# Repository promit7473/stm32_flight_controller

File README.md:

# STM32 Autonomous Quadcopter Flight Controller

A bare-metal flight controller for a quadcopter, running a **250 Hz** control
loop on an STM32F103C8T6 (Cortex-M3, 72 MHz, no FPU). It fuses a gyroscope,
accelerometer, magnetometer, barometer and GPS into an attitude and position
estimate, and closes six control loops around it: three rate loops, an
attitude cascade, altitude hold, and GPS position hold.

No flight stack, no RTOS, no libraries beyond `Wire` and `EEPROM`. Every
transform, filter and controller here is written out explicitly, which is why
this document can state exactly what the aircraft computes on each of its
250 loops per second.

Built in 2023, then flown, re-tuned and upgraded repeatedly across my
undergraduate years. The airframe, wiring and gains in this repository are the
state it reached after those iterations, not a first attempt.

<p align="center">
  <em>Take-off under its own control.
  Full 18 s flight: <a href="media/test_flight_540p.mp4">test_flight_540p.mp4</a></em>
</p>

<p align="center">
  <em>Hand-soldered on perfboard: STM32 board, MPU-6050, MS5611, HMC5883L,
  GPS and the 433 MHz telemetry radio, wired to four ESCs.</em>
</p>

---

## Hardware

### Module-carrier PCB — Rev A prototype

The new carrier is a **90 × 70 mm, two-layer PCB** for the Blue Pill and
plug-in IMU, compass and barometer modules, with connectors for GPS, telemetry,
a PPM-sum receiver and four ESCs. It is intended for an F450-style build;
the 80 × 60 mm mounting pattern requires a verified adapter or standoffs,
not an assumed direct fit to the frame.

These are **CAD previews, not photographs of built hardware**. The Blue Pill
uses a detailed community model; the three sensor modules are illustrative
approximations. The historical flight photos above show the earlier perfboard
controller, not validation of this new PCB.

- [KiCad project, PCB and assembly notes](hardware/stm32_f450_carrier_rev_a/README.md)
- [Gerbers and drill files](hardware/stm32_f450_carrier_rev_a/fabrication/)
  · [downloadable fabrication ZIP](hardware/stm32_f450_carrier_rev_a/stm32_f450_carrier_rev_a_gerbers.zip)
- [BOM](hardware/stm32_f450_carrier_rev_a/BOM.csv)
  · [connector pin map](hardware/stm32_f450_carrier_rev_a/pinmap.csv)
- [Mechanical assumptions and fit checks](hardware/stm32_f450_carrier_rev_a/MECHANICAL_BASELINE.md)
  · [3D model attribution and optional download](hardware/stm32_f450_carrier_rev_a/MODEL_SOURCES.md)

The current [KiCad DRC report](hardware/stm32_f450_carrier_rev_a/drc.rpt)
has **0 violations and 0 unconnected pads**. This checks layout rules, not
electrical correctness or flight readiness. Before ordering: confirm actual
module pinouts, frame fit and power paths; complete a native schematic and
electrical review; then perform current-limited bench tests without propellers.
Complete sourced sensor CAD models are still outstanding.

### Devices and firmware interfaces

| Part | Device | Interface |
| --- | --- | --- |
| MCU | STM32F103C8T6, 72 MHz Cortex-M3, 20 KB RAM, no FPU | — |
| IMU | MPU-6050, gyro ±500 °/s and accelerometer ±8 g | I²C2 @ 400 kHz |
| Magnetometer | HMC5883L | I²C2 @ 400 kHz |
| Barometer | MS5611, 24-bit pressure and temperature | I²C2 @ 400 kHz |
| GNSS | u-blox, UBX binary at 57 600 baud, 5 Hz | USART1 |
| Telemetry | 433 MHz link to a ground receiver | bit-banged, 1 byte/loop |
| Receiver | 6 channels decoded from one PPM/CPPM-sum signal | TIM2, PA0 |
| Motors | 4 × ESC, 1000–2000 µs pulses at 250 Hz | TIM4 PWM |

The absence of an FPU is the single most important fact about this target.
Every `float` operation is a software routine, so the loop budget below is
dominated by arithmetic that would be free on an F4.

---

## Control architecture

One loop, 4000 µs, no scheduler. The order matters: sensors are read first,
the estimate is updated, controllers run on that estimate, and the motor
pulses are written last so they are as fresh as possible.

```
   ┌─ 250 Hz, Δt = 4 ms ─────────────────────────────────────────────┐
   │  read IMU ─ barometer ─ compass ─ GPS                           │
   │        ↓                                                        │
   │  attitude estimate  (complementary filter, §2)                  │
   │        ↓                                                        │
   │  altitude hold (§5) ── GPS position hold (§6) ── heading lock   │
   │        ↓                                                        │
   │  angle → rate cascade (§3)                                      │
   │        ↓                                                        │
   │  three rate PIDs: roll, pitch, yaw (§3)                         │
   │        ↓                                                        │
   │  motor mixing + battery compensation (§4)                       │
   │        ↓                                                        │
   │  TIM4 compare registers → ESCs                                  │
   └─────────────────────────────────────────────────────────────────┘
```

The loop is **hard real time by construction**: it busy-waits on `micros()`
until 4000 µs have elapsed, and raises an error flag if the work took longer
than 4050 µs. Section 8 explains why the timing is not merely a nicety.

---

## 1. Sensor scaling

The MPU-6050 is configured for ±500 °/s, which the datasheet specifies as
**65.5 LSB per °/s**. Angular rate in engineering units is therefore

```math
\omega = \frac{g_{\text{raw}}}{65.5}\ \ [^\circ/\text{s}]
```

Raw rates are noisy, so each axis is low-pass filtered with a first-order IIR:

```math
\omega_f[k] = 0.7\,\omega_f[k-1] + 0.3\,\omega[k]
```

This is an exponential moving average with smoothing factor $\alpha = 0.3$.
Its time constant and −3 dB cutoff at $f_s = 250$ Hz are

```math
\tau = \frac{\Delta t}{\alpha} \approx 13\ \text{ms},
\qquad f_c = \frac{-\ln(1-\alpha)}{2\pi\,\Delta t} \approx 14\ \text{Hz}
```

Low enough to reject propeller vibration, high enough to leave the rate loop
phase margin intact.

## 2. Attitude estimation

**Integration.** Each axis integrates rate into angle:

```math
\theta[k] = \theta[k-1] + \omega\,\Delta t
```

In the code this appears as the constant `0.0000611`, which is exactly

```math
\frac{1}{250 \times 65.5} = \frac{\Delta t}{\text{LSB per }^\circ/\text{s}}
= 6.107\times10^{-5}
```

so the multiply converts raw counts straight to degrees, folding the sensor
scale and the sample period into one constant.

**Yaw coupling.** Roll and pitch are defined in a frame that yaws with the
aircraft, so when the airframe rotates about $z$ some roll becomes pitch and
vice versa. To first order in a single 4 ms step:

```math
\theta_p \mathrel{-}= \theta_r \sin(\omega_y \Delta t), \qquad
\theta_r \mathrel{+}= \theta_p \sin(\omega_y \Delta t)
```

The code's `0.000001066` is $6.107\times10^{-5} \times \pi/180$, converting
the yaw step to radians for `sin()` in the same constant.

**Gravity reference.** The accelerometer gives an absolute but noisy attitude,
valid only when specific force is dominated by gravity:

```math
\lVert a \rVert = \sqrt{a_x^2 + a_y^2 + a_z^2}, \qquad
\theta_{p,\text{acc}} = \arcsin\!\left(\frac{a_y}{\lVert a \rVert}\right),
\qquad
\theta_{r,\text{acc}} = \arcsin\!\left(\frac{a_x}{\lVert a \rVert}\right)
```

Both are guarded by `abs(a) < |a|` so `asin` can never receive an argument
outside $[-1,1]$ and return NaN. A single NaN here would propagate into the
angles, the setpoints and the motor outputs within one loop.

**Complementary filter.** Gyro integration drifts; the accelerometer is noisy
but unbiased. Blending them:

```math
\theta = 0.9996\,(\theta + \omega\Delta t) + 0.0004\,\theta_{\text{acc}}
```

This is a first-order complementary filter with

```math
\tau = \Delta t\,\frac{\alpha}{1-\alpha}
= 0.004 \times \frac{0.9996}{0.0004} \approx 10\ \text{s}
```

Gyro data passes above ~0.016 Hz, accelerometer below. Ten seconds is long
enough that a coordinated turn does not tilt the estimate, short enough to
wash out gyro bias.

**Heading.** The magnetometer is tilt-compensated by rotating the measurement
into the horizontal plane using the current roll $\phi$ and pitch $\theta$:

```math
X_h = X\cos\theta + Y\sin\phi\sin\theta - Z\cos\phi\sin\theta
```
```math
Y_h = Y\cos\phi + Z\sin\phi
```
```math
\psi = \mathrm{atan2}(Y_h,\,X_h) + \delta
```

where $\delta$ is magnetic declination. The gyro-integrated yaw is then pulled
toward this heading by $1/1200$ of the deviation each loop, a ~4.8 s time
constant, which keeps yaw absolute without letting magnetic disturbance jerk
the estimate.

## 3. Rate control and the attitude cascade

The inner loop regulates **angular rate**, not angle. Stick position becomes a
rate demand, with a 16 µs dead band around centre:

```math
\omega_{sp} = \frac{u_{\text{stick}} - 1500 \mp 8}{3} - 15\,\theta
```

Dividing by 3 gives a full-stick rate of $(500-8)/3 \approx 164\ ^\circ/\text{s}$.

The $-15\theta$ term is the **outer attitude loop**: a proportional controller
on angle whose output is a rate demand. Level flight is the fixed point, and
holding the stick over commands a steady rate rather than a steady angle. The
cascade is therefore

```math
\underbrace{\theta \to \omega_{sp}}_{\text{P, gain }15}
\quad\longrightarrow\quad
\underbrace{\omega_{sp} \to u}_{\text{PID}}
```

Each axis then runs a discrete PID on the rate error $e = \omega_f - \omega_{sp}$:

```math
I[k] = \mathrm{clamp}\big(I[k-1] + K_i\,e[k],\ \pm u_{max}\big)
```
```math
u[k] = \mathrm{clamp}\big(K_p\,e[k] + I[k] + K_d\,(e[k]-e[k-1]),\ \pm u_{max}\big)
```

Two implementation details worth stating plainly, because they change what the
gains mean:

- **$K_i$ is per loop, not per second.** The integral accumulates $K_i e$ once
  per iteration, so the continuous-time integral gain is $K_i f_s = 250 K_i$.
  With $K_i = 0.04$ that is an effective $10\ \text{s}^{-1}$.
- **$K_d$ acts on the error difference, not a derivative.** There is no
  division by $\Delta t$, so the continuous-time derivative gain is
  $K_d \Delta t = K_d / 250$.

The integrator is clamped to the same limit as the output, which is what stops
integral wind-up from parking a motor at full throttle after a long
disturbance.

| Axis | $K_p$ | $K_i$ | $K_d$ | limit |
| --- | --- | --- | --- | --- |
| Roll / Pitch | 1.3 | 0.04 | 18.0 | ±400 |
| Yaw | 4.0 | 0.02 | 0.0 | ±400 |
| Altitude | 1.4 | 0.2 | 0.75 | ±400 |

Yaw carries no derivative term: the axis has the largest rotational inertia
and the least aerodynamic damping, so D would amplify motor noise for very
little phase lead.

## 4. Motor mixing

For an X configuration, each rotor contributes to all three torques. With
throttle $T$ and controller outputs $u_r, u_p, u_y$:

```math
\begin{bmatrix} M_{FR} \\ M_{RR} \\ M_{RL} \\ M_{FL} \end{bmatrix}
=
T +
\begin{bmatrix}
-1 & +1 & -1 \\
+1 & +1 & +1 \\
+1 & -1 & -1 \\
-1 & -1 & +1
\end{bmatrix}
\begin{bmatrix} u_p \\ u_r \\ u_y \end{bmatrix}
```

The yaw column is the pattern that makes a quadcopter work: diagonal pairs
spin the same way, so differential thrust between the two pairs produces a net
reaction torque about $z$ without disturbing roll or pitch.

Outputs are clamped to `[motor_idle, 2000]` µs, and throttle is capped at
1800 µs so that ±200 µs of control authority survives at full stick. **A
saturated mixer cannot stabilise the aircraft**, which is what that headroom
protects.

**Battery compensation.** As the pack sags, a given pulse width produces less
thrust. The mixer adds an open-loop correction:

```math
M_i \mathrel{+}= (12.40 - V_{batt})\,k_{comp}
```

with $k_{comp} = 40$ µs per volt, applied only while $6 < V_{batt} < 12.40$ V
so a disconnected sensor cannot command full throttle. Battery voltage itself
is filtered:

```math
V[k] = 0.92\,V[k-1] + \frac{\text{ADC}}{1410.1}
```

## 5. Altitude hold

The MS5611 returns raw pressure $D_1$ and temperature $D_2$, which the
datasheet's second-order compensation converts to pressure using the six
factory calibration coefficients $C_1 \ldots C_6$:

```math
dT = D_2 - C_5 \cdot 2^{8}
```
```math
\text{OFF} = C_2 \cdot 2^{16} + \frac{C_4 \, dT}{2^{7}}, \qquad
\text{SENS} = C_1 \cdot 2^{15} + \frac{C_3 \, dT}{2^{8}}
```
```math
P = \frac{\dfrac{D_1 \cdot \text{SENS}}{2^{21}} - \text{OFF}}{2^{15}}
```

Conversion takes ~9 ms, longer than one control loop, so the driver is a small
state machine spread over several iterations: request, wait, read, compute.
Temperature is re-read only every 20th cycle, since it changes far more slowly
than pressure, and is itself averaged over 5 samples to reject spikes.

Pressure is smoothed by a 20-sample moving average and then split into fast
and slow components; their difference is the vertical rate signal that the
altitude PID damps. Altitude hold regulates pressure directly rather than
converting to metres, since only the *difference* from the hold point matters.

## 6. GPS position hold

Position error is held in raw 1e-7° units. Each axis runs a PD controller,
where the derivative is a moving sum of recent error changes rather than a
single difference, which is what makes it usable given 5 Hz GPS into a 250 Hz
loop:

```math
u_{north} = K_p\,e_{lat} + K_d \sum \Delta e_{lat}, \qquad
u_{east} = K_p\,e_{lon} + K_d \sum \Delta e_{lon}
```

with $K_p = 2.7$, $K_d = 6.5$. Between GPS fixes the position estimate is
linearly interpolated forward so the controller sees a smooth signal instead
of a 5 Hz staircase.

The correction is computed in the **north-east frame** and must be rotated
into the **body frame** before it can be added to the stick commands:

```math
u_{roll} = u_{east}\cos\psi + u_{north}\cos(\psi - 90^\circ)
```
```math
u_{pitch} = u_{north}\cos\psi + u_{east}\cos(\psi + 90^\circ)
```

This is a rotation by heading $\psi$, written with cosines of shifted angles
rather than a sine so both terms share one trigonometric form. Output is
clamped to ±300 µs, roughly a 6° tilt demand.

## 7. Heading lock

With heading lock engaged, the stick frame stays fixed to the heading captured
at arming, so "forward" means the same direction regardless of which way the
airframe points. The commands are rotated by the deviation
$\Delta\psi = \psi - \psi_{lock}$:

```math
u_{roll} = 1500 + (u_1 - 1500)\cos\Delta\psi + (u_2 - 1500)\cos(\Delta\psi - 90^\circ)
```
```math
u_{pitch} = 1500 + (u_2 - 1500)\cos\Delta\psi + (u_1 - 1500)\cos(\Delta\psi + 90^\circ)
```

## 8. Why the loop period is load-bearing

$\Delta t$ is not a parameter that can be retuned; it is **compiled into the
constants**. `0.0000611` embeds $1/250$, and `0.000001066` embeds it again.
Running the loop at 200 Hz without touching those constants would scale every
integrated angle by 1.25 and the attitude estimate would be silently wrong,
with no error flag raised.

This is why the loop busy-waits rather than simply running as fast as it can,
and why exceeding 4050 µs sets an error. The margin is thin: 4050 µs against a
4000 µs period is **1.25%**. On a 72 MHz core with no FPU, adding a handful of
`float` divisions inside the loop is enough to consume it.

---

## Findings

Behaviour-preserving refactoring was the goal, so the following were
**documented rather than silently changed**. Each alters flight behaviour, and
that is the pilot's call, not the refactorer's.

**1. A tautological guard in the vertical-acceleration filter.**
`vertical_speed.ino` reads:

```c
if (acc_total_vector - acc_z_average_total < 400 || acc_total_vector - acc_z_average_total > 400)
```

The condition is `x < 400 || x > 400`, true for every value of `x` except
exactly 400, so the guard never gates anything. The intent was almost
certainly a symmetric dead band, `x < -400 || x > 400`. Correcting it would
change how aggressively the integrated vertical acceleration is bled off, and
therefore the feel of altitude hold.

**2. `π` approximated as 3.14 in the heading calculation.**
`compass.ino` converts the `atan2` result with `180 / 3.14` where the rest of
the codebase uses the correct `57.296`. The ratio is
$\frac{180/3.14}{180/\pi} = 1.00051$, a 0.05% scale error, about 0.18° over a
full rotation. Small, but it makes heading disagree slightly with every other
angle in the system.

**3. Software `pow()` for powers of two.**
The pressure computation calls `pow(2,7)`, `pow(2,8)`, `pow(2,15)` and
`pow(2,21)`. On a core without an FPU each is a software floating-point
routine costing hundreds of cycles, where the values are exact compile-time
constants. Replacing them is provably identical numerically, and is the single
cheapest way to buy back loop-time margin (§8).

---

## Repository layout

```
firmware/
  flight_controller/    the flight controller itself
  test_bench/           sensor and receiver bring-up, run this first
  telemetry_receiver/   ground-station side of the 433 MHz link
docs/                   schematic, and the script that generates it
hardware/
  stm32_f450_carrier_rev_a/  KiCad PCB, previews, BOM, pin map and prototype fabrication files
tools/                  media tooling
media/                  build photos, flight GIF and footage
```

`docs/make_schematic.py` regenerates the schematic, so it stays in step with
the firmware rather than drifting the way a hand-drawn one would.

`tools/make_card_clip.py` cuts a 16:9 clip from the portrait flight footage by
tracking the drone and panning a crop window to follow it, so the aircraft
stays framed from the ground to altitude instead of climbing out of a fixed
crop. Run it with `--check` first: it writes a contact sheet with the
detection and the crop window drawn on, which is the only reliable way to see
whether the track held.

## Wiring

### Pin assignment

Taken from the firmware, not from a drawing.

| Pin | Peripheral | Net | Connects to |
| --- | --- | --- | --- |
| PA0 | TIM2_CH1 input capture | `PPM` | RC receiver, PPM out |
| PB10 | I2C2 SCL | `SCL` | MPU-6050, HMC5883L, MS5611 |
| PB11 | I2C2 SDA | `SDA` | MPU-6050, HMC5883L, MS5611 |
| PA9 | USART1 TX | `GPS_RX` | u-blox GNSS, RX |
| PA10 | USART1 RX | `GPS_TX` | u-blox GNSS, TX |
| PB0 | GPIO | `TLM_TX` | 433 MHz telemetry radio |
| PA4 | ADC_IN4 | `VBAT_SNS` | 10k/1k divider from the pack |
| PB6 | TIM4_CH1 PWM | `ESC1` | front-right motor, CCW |
| PB7 | TIM4_CH2 PWM | `ESC2` | rear-right motor, CW |
| PB8 | TIM4_CH3 PWM | `ESC3` | rear-left motor, CCW |
| PB9 | TIM4_CH4 PWM | `ESC4` | front-left motor, CW |
| PB3 | GPIO | `LED_GRN` | green LED, flight mode |
| PB4 | GPIO | `LED_RED` | red LED, error |
| PC13 | GPIO | `LED_BRD` | on-board LED, GPS fix, inverted |

Every connection above is cross-checked against the firmware rather than
copied from a drawing. The timer compare registers give the ESC pins, the
input-capture configuration gives the receiver pin, `Serial1` gives the GPS
pins, and `HWire(2, ...)` gives the I2C pins.

The battery divider is confirmed arithmetically: the firmware divides the ADC
count by 112.81, and a 10k/1k divider into a 12-bit ADC on a 3.3 V reference
gives 4095 / (3.3 x 11) = 112.8. The constant in the code and the resistor
values agree, so neither is guesswork.

## Building

The two STM32 sketches need the **libmaple** core
([`Arduino_STM32`](https://github.com/rogerclarkmelbourne/Arduino_STM32)), not
the official STM32 core. The code uses libmaple APIs directly:
`TIMER4_BASE->CCR1`, `afio_cfg_debug_ports()`, `TwoWire HWire(2, I2C_FAST_MODE)`.
That core also needs `arduino:sam` installed, which is where its
`arm-none-eabi-gcc` comes from.

**The telemetry receiver is not an STM32 sketch.** It targets an AVR (Arduino
Uno) and uses `TCCR2A`/`TCCR2B`, so it must be compiled for `arduino:avr:uno`
and needs the `LiquidCrystal` library. Building it for the STM32 fails with
undeclared-register errors that look alarming and mean only that the board is
wrong.

| Sketch | Board (FQBN) | Flash | RAM |
| --- | --- | --- | --- |
| `flight_controller` | `Arduino_STM32:STM32F1:genericSTM32F103C` | 43 280 B (66%) | 4 072 B (19%) |
| `test_bench` | `Arduino_STM32:STM32F1:genericSTM32F103C` | 40 088 B (61%) | 2 616 B (12%) |
| `telemetry_receiver` | `arduino:avr:uno` | 9 424 B (29%) | 660 B (32%) |

All three figures are from a clean build of this tree.

Bring the aircraft up in this order. Each step depends on the one before it:

1. **`test_bench`** — verifies I²C devices respond, receiver channels map to
   the right axes, and motor rotation directions are correct.
2. **Level and compass calibration** — both sticks to a corner while disarmed,
   stored in EEPROM.
3. **`flight_controller`** — propellers off for the first arm.

## Safety

**Remove the propellers** for every bench test. An armed quadcopter with a
mis-mapped receiver channel will apply full corrective thrust in the wrong
direction. The mixer has no notion of whether the airframe is in the air.

The arming sequence is deliberately two-handed and hard to trigger by
accident: throttle low **and** yaw left to arm, throttle low **and** yaw right
to disarm.

---

## Credits

Based on the YMFC-32 flight controller by Joop Brokking. This repository is my
build of it: my airframe, my wiring, my tuning, my flights, refactored firmware.

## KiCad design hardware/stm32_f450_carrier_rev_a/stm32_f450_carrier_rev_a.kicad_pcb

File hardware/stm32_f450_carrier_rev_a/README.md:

# STM32 F450 module-carrier PCB — Rev A

This folder is the KiCad 10 prototype package for the module carrier
used by the STM32 flight-controller firmware.

## Open and inspect

- `stm32_f450_carrier_rev_a.kicad_pro` — KiCad project.
- `stm32_f450_carrier_rev_a.kicad_pcb` — routed two-layer PCB.
- `board-preview.png` and `board-top.png` — rendered board views.
- `assembled-preview.png` — populated view with a published Blue Pill model
  and illustrative sensor module models.
- `3dmodels/carrier_assembly.wrl` — portable assembly model attached to J1;
  keep this folder beside the board file when opening KiCad's 3D Viewer.
- `board-layout.svg` — printable 1:1 fit-check drawing.
- `pinmap.csv` — connector-to-MCU mapping.
- `BOM.csv` — assembly bill of materials.
- `drc.rpt` — KiCad DRC result (zero violations; zero unconnected pads).
- `functional-schematic.svg` — firmware-level wiring reference from the source repository.
- There is no native `.kicad_sch` schematic or ERC report yet.
- `fabrication/` — Gerbers, plated/non-plated drill files, and drill maps.

## Fabrication assumptions

- 2 layers, FR-4, 1.6 mm thickness, 1 oz copper.
- Default finish and solder-mask color are acceptable.
- Board outline is 90 × 70 mm.

## Prototype warning

The preview images use the complete published YAAJ Blue Pill CAD assembly,
including sockets, USB, jumpers, components and SWD header. That third-party
model is not bundled in Git because its redistribution license is unconfirmed.
See `MODEL_SOURCES.md` for the optional download and placement instructions.
Without it, KiCad will omit the Blue Pill body from the 3D view; copper and
fabrication outputs are unaffected. The sensor models remain approximate illustrations.
The revised placement removes the modeled overlap and sensor overhang.
Verify real module envelopes and orientation before manufacture; copper DRC
does not establish module compatibility. Previous exports used incorrect
Blue Pill socket spacing and pin ordering and are superseded by this update.
GPS, receiver, telemetry radio and ESC units are external; their carrier
connectors are shown, not those external units. Model labels may not appear
in KiCad because its VRML importer does not render Text nodes.

This is flight-critical prototype hardware, not a certified flight controller.
The DRC report lists ignored checks, including missing footprint courtyards;
zero reported violations is not a complete mechanical-clearance review.
The fuse/diode protect the J11 input path; J6/ESC1 connects directly to the
5 V rail. Review backfeeding and power-source selection before connecting
USB, an external supply or any ESC BEC together.
Verify actual clone-module pin order and socket spacing before manufacture.
Continuity-test every power rail, bring it up with current limiting, validate
all sensor axes and motor mapping, and perform bench tests with propellers
removed before any restrained or free-flight test.

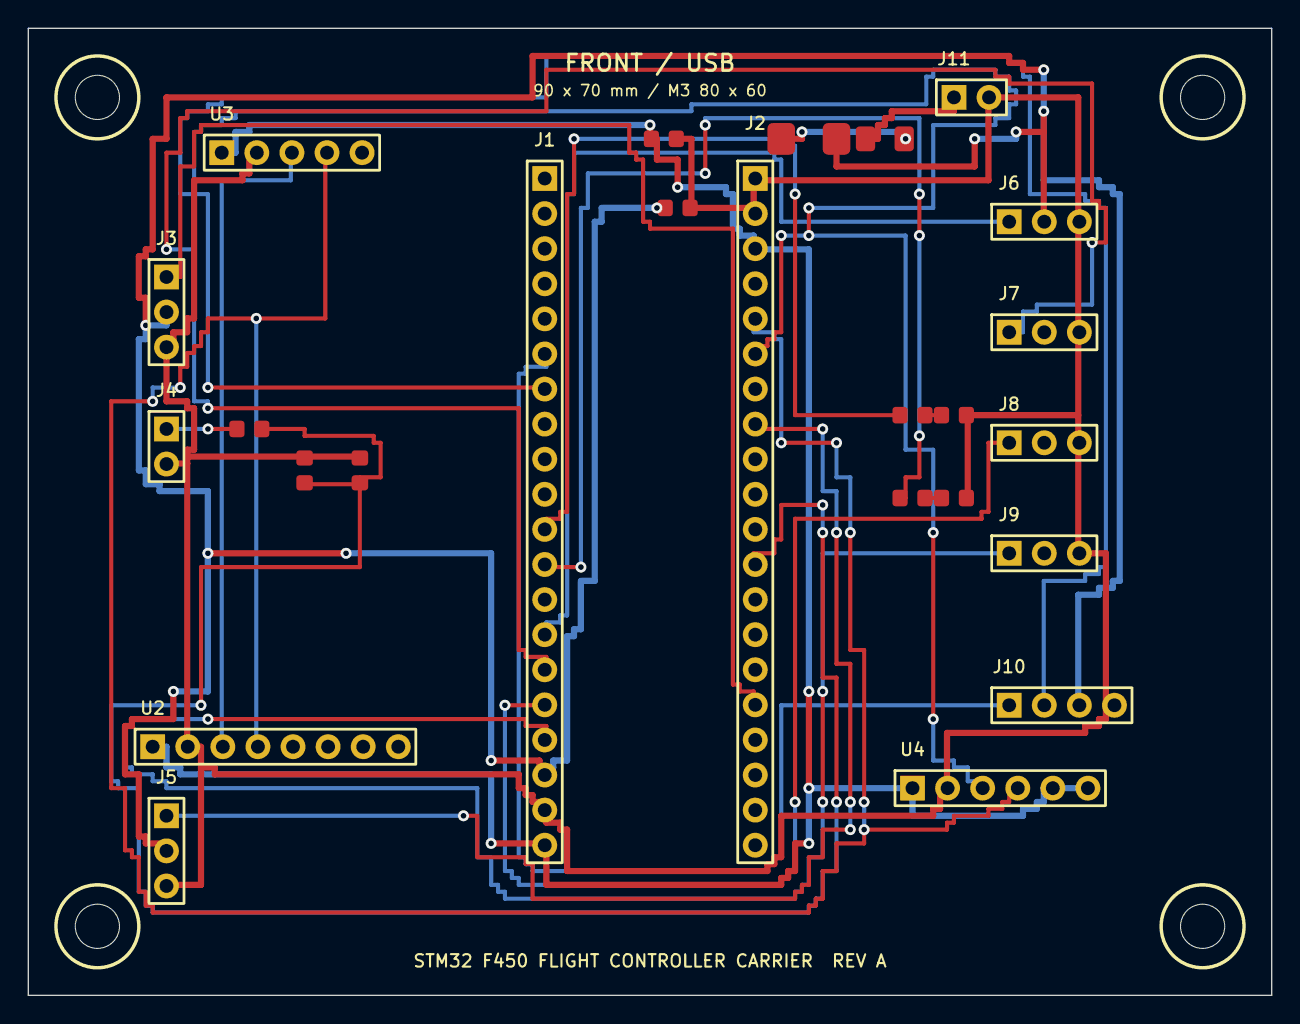
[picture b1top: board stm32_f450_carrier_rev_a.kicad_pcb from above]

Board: 2 copper layers, 90.0 x 70.0 mm, 29 parts (0 on the bottom side), 21 nets.

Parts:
C1, C3: 100n; Carrier_0603
C2: 10u; Carrier_0603
D1: GREEN_LED; Carrier_0603
D2: RED_LED; Carrier_0603
D3: SS14_SMA; Carrier_0603
F1: PTC_500mA_1206; Carrier_0603
H1, H2, H3, H4: M3; MountingHole_M3
J1: BLUEPILL_LEFT; Carrier_Header
J2: BLUEPILL_RIGHT; Carrier_Header
J3: RC_PPM; Carrier_Header
J4: BATTERY_SENSE; Carrier_Header
J5: TELEMETRY; Carrier_Header
J6: ESC1_FRONT_RIGHT; Carrier_Header
J7: ESC2_REAR_RIGHT; Carrier_Header
J8: ESC3_REAR_LEFT; Carrier_Header
J9: ESC4_FRONT_LEFT; Carrier_Header
J10: GPS_UBLOX; Carrier_Header
J11: BEC_5V_INPUT; Carrier_Header
R1, R2: 330R; Carrier_0603
R3: 10k; Carrier_0603
R4: 1k; Carrier_0603
U2: GY521_MPU6050; Carrier_Header
U3: GY271_HMC5883L; Carrier_Header
U4: GY63_MS5611; Carrier_Header

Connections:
3V3: C3.1, J1.20, J2.3, U2.1, U3.1, U4.1, U4.5, U4.6
5V: C2.1, D3.2, J1.18, J3.2, J5.2, J6.2, J10.3
5V_IN: F1.1, J11.1
ESC1: J1.14, J6.1
ESC2: J1.15, J7.1
ESC3: J1.16, J8.1
ESC4: J1.17, J9.1
FUSED_5V: D3.1, F1.2
GND: C1.2, C2.2, C3.2, D1.2, D2.2, J1.19, J2.1, J2.2, J3.3, J4.2, J5.3, J6.3, J7.3, J8.3, J9.3, J10.4, J11.2, R4.2, U2.2, U3.2, U4.2
GPS_RX: J1.6, J10.1
GPS_TX: J1.7, J10.2
LED_GRN: J1.11, R1.1
LED_GRN_A: D1.1, R1.2
LED_RED: J1.12, R2.1
LED_RED_A: D2.1, R2.2
PPM: J2.16, J3.1
SCL: J2.6, U2.3, U3.3, U4.3
SDA: J2.5, U2.4, U3.4, U4.4
TLM_TX: J2.8, J5.1
VBAT: J4.1, R3.1
VBAT_SNS: C1.1, J2.12, R3.2, R4.1

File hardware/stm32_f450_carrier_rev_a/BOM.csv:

Reference,Quantity,Description,Value / footprint
J1 J2,2,Blue Pill female socket,1x20 2.54 mm
J3-J11,9,External module/servo headers,2.54 mm through-hole
U2,1,MPU-6050 GY-521 module socket,1x8 2.54 mm
U3,1,HMC5883L GY-271 module socket,1x5 2.54 mm
U4,1,MS5611 GY-63 module socket,1x6 2.54 mm
F1,1,Resettable fuse,500 mA 1206
D3,1,Schottky reverse-polarity diode,SS14 SMA
R1 R2,2,LED current resistor,330 ohm
R3,1,Battery divider upper resistor,10 kohm 1%
R4,1,Battery divider lower resistor,1 kohm 1%
C1 C3,2,Decoupling/filter capacitor,100 nF
C2,1,Input bulk capacitor,10 uF
D1,1,Green status LED,0603
D2,1,Red status LED,0603
H1-H4,4,Mounting hole,M3 with vibration grommet/standoff

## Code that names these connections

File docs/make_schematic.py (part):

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s.append(txt(MX + MW / 2, MY + 57, "20 KB RAM   no FPU   3.3 V", 9.5, MUTED, "400", "middle"))
s.append(line(MX, MY + 68, MX + MW, MY + 68, ACC, 1.0))

left = [("PA0", "TIM2_CH1", "PPM", 100),
        ("PB10", "I2C2_SCL", "SCL", 140),
        ("PB11", "I2C2_SDA", "SDA", 165),
        ("PA9", "USART1_TX", "GPS_RX", 205),
        ("PA10", "USART1_RX", "GPS_TX", 230),
        ("PB0", "GPIO", "TLM_TX", 270),
        ("PA4", "ADC_IN4", "VBAT_SNS", 310)]
right = [("PB6", "TIM4_CH1", "ESC1", 100),
         ("PB7", "TIM4_CH2", "ESC2", 125),
         ("PB8", "TIM4_CH3", "ESC3", 150),
         ("PB9", "TIM4_CH4", "ESC4", 175),
         ("PB3", "GPIO", "LED_GRN", 220),
         ("PB4", "GPIO", "LED_RED", 245),
         ("PC13", "GPIO", "LED_BRD", 270)]

for pin, fn, net, dy in left:
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mid = DY + 7 + 4.6 * 6 + 7
s.append(junction(DX, mid))
s.append(line(DX, mid, DX + 92, mid, NET, 1.4))
s.append(net_label(DX + 92, mid, "VBAT_SNS", "right"))
s.append(resistor(DX, mid, "R4", "1k"))
bot = mid + 7 + 4.6 * 6 + 7
s.append(line(DX, bot, DX, bot + 6))
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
